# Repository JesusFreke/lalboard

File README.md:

##### lalboard - A 3D-printed keyboard inspired by the DataHand.

## Links
[More Images](https://github.com/JesusFreke/lalboard/wiki/Images)

[120 WPM Typing Demo](https://www.youtube.com/watch?v=oMhOIgrdeE0)

[V2 Project Logs (hackaday.io)](http://lalboard.com)

Online viewer for cluster assemblies:
- [finger](https://a360.co/3vxlLLL)
- [left thumb](https://a360.co/3c63TzE)
- [right thumb](https://a360.co/3c6tvws)

## Project Details
I am a long-time user of a DataHand keyboard. With the scarcity and rising cost of second hand
DataHands these days, I wanted to ensure that I always had access to a DataHand-like keyboard. And
so this project was born.

The overall functionality of the lalboard is obviously heavily based on the DataHand, but I designed
all of the specific key mechanisms, etc. from scratch, to be printable on a normal hobby-level
FDM printer.

With my DataHand, I never felt like I could get the keys positioned *quite right* for my hand. So
one of my primary focuses with the lalboard was adjustability. Each key cluster can be independently
adjusted in all 6 degrees of freedom to some extent.

Most parts need to be printed in a very opaque PLA, but there are a few parts that don't work well
in PLA which should be printed in polycarbonate or similar material, for its strength and heat
resistance.

##### Key Mechanisms

All keys use a pair of magnets to provide the clickiness and key return force, and an IR LED and
phototransistor for detecting a keypress. They are all held in place only with magnets, so they
are easily removable for cleaning, etc.

The feel/clickiness of the keys was another focus area. I tried to get them to feel as similar to
those on a DataHand as possible. They require roughly the same amount of force, and have that same
unique clicky feel due to the magnetic holding force.

##### Adjustability

The key clusters have a trio of standoffs that are designed to be mounted onto a steel sheet with
magnets. Each standoff has an adjustable height, and is mounted to the key cluster via a
ball socket. This provides a limited 6 degrees of freedom in adjusting the angle and position of
each key cluster, in order to get it perfectly positioned for your hands.

##### Electronics

This design uses copper traces that are cut from adhesive-backed copper tape using a vinyl cutter,
and applied to the bottom of 3D-printed "pcbs" printed with polycarbonate for its excellent heat
resistance during soldering. There are currently no designs for actual pcbs, but I don't think it
should be difficult to do. If someone wants to tackle that, I'm happy to give pointers or otherwise
help in any way I can :)

Each side of the keyboard uses an independent teensy 2.0 board, and are connected with 4 wires
between them to enable communication via i2c. Only one side of the keyboard actually needs to be
plugged into USB. The teensy's run a modified version of the
[teensyhand](https://github.com/JesusFreke/teensyhand) firmware.

##### Handrest

The handrest was first molded for my wrist in plasticine clay, and then scanned in using the
[meshroom](https://github.com/alicevision/meshroom) photogrammetry software. Since they were molded
for my wrists specifically, I'm not sure how "one-size-fits-all" they are, or how comfortable they
would be for someone else to use.

##### [BOM](https://github.com/JesusFreke/lalboard/wiki/BOM)

##### [Printing tips & instructions](https://github.com/JesusFreke/lalboard/wiki/Printing-tips-&-instructions)

##### [Preparing the Vinyl-cut PCBs](https://github.com/JesusFreke/lalboard/wiki/Vinyl-Cut-PCBs)

--------

Note: This is not an officially supported Google product.

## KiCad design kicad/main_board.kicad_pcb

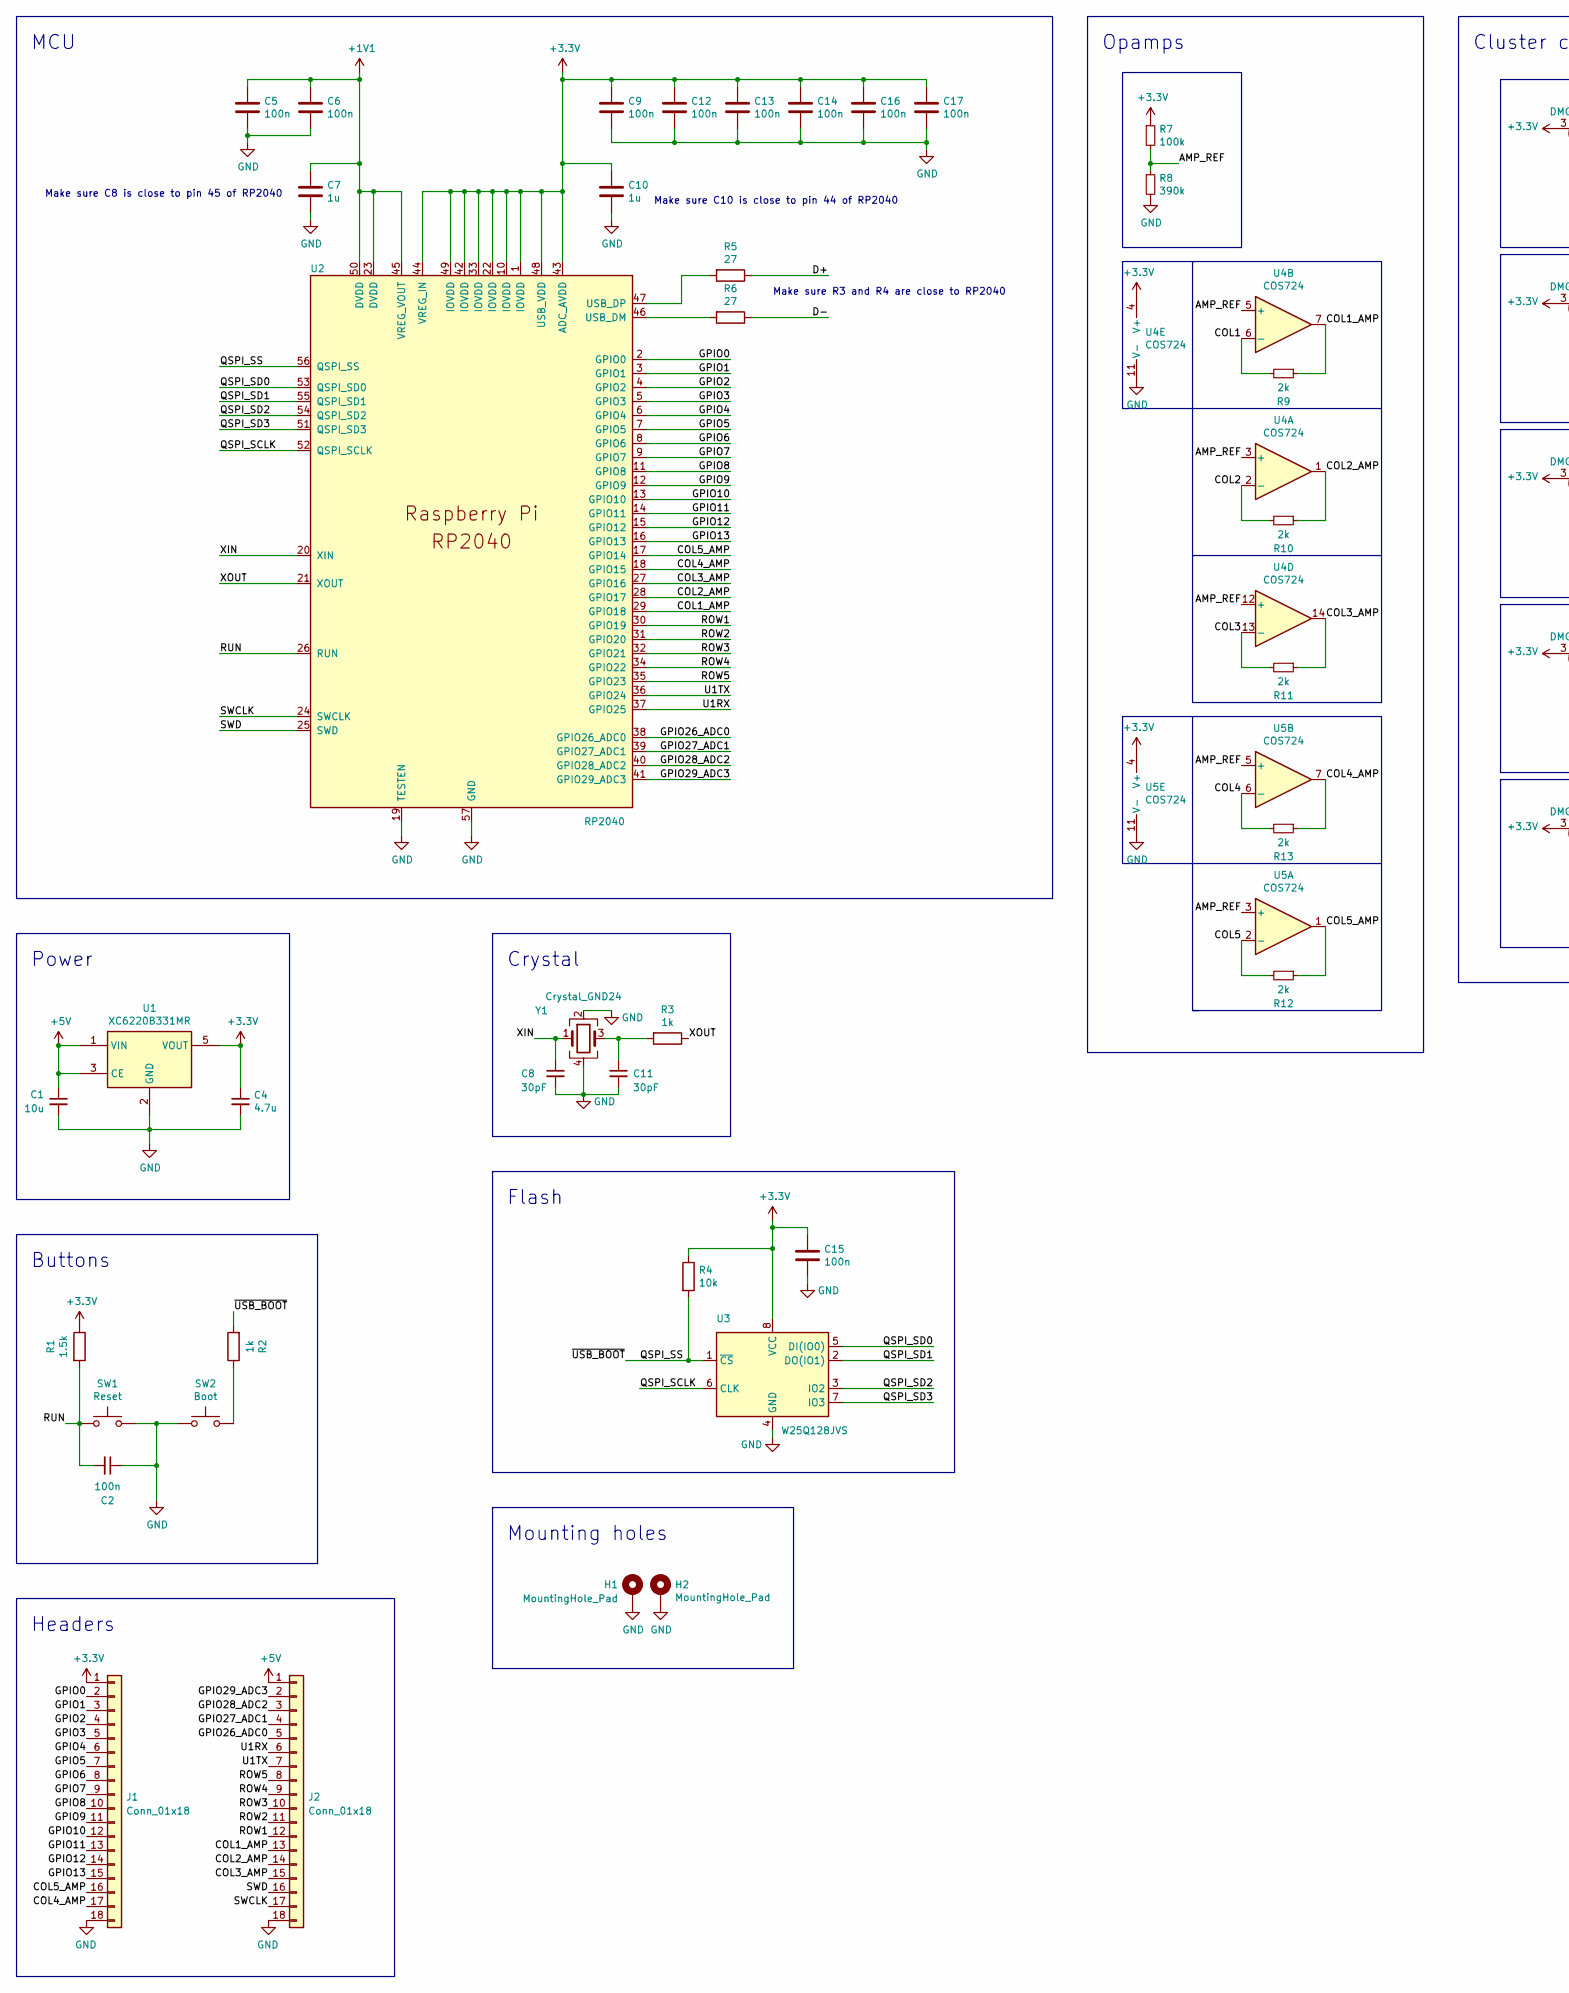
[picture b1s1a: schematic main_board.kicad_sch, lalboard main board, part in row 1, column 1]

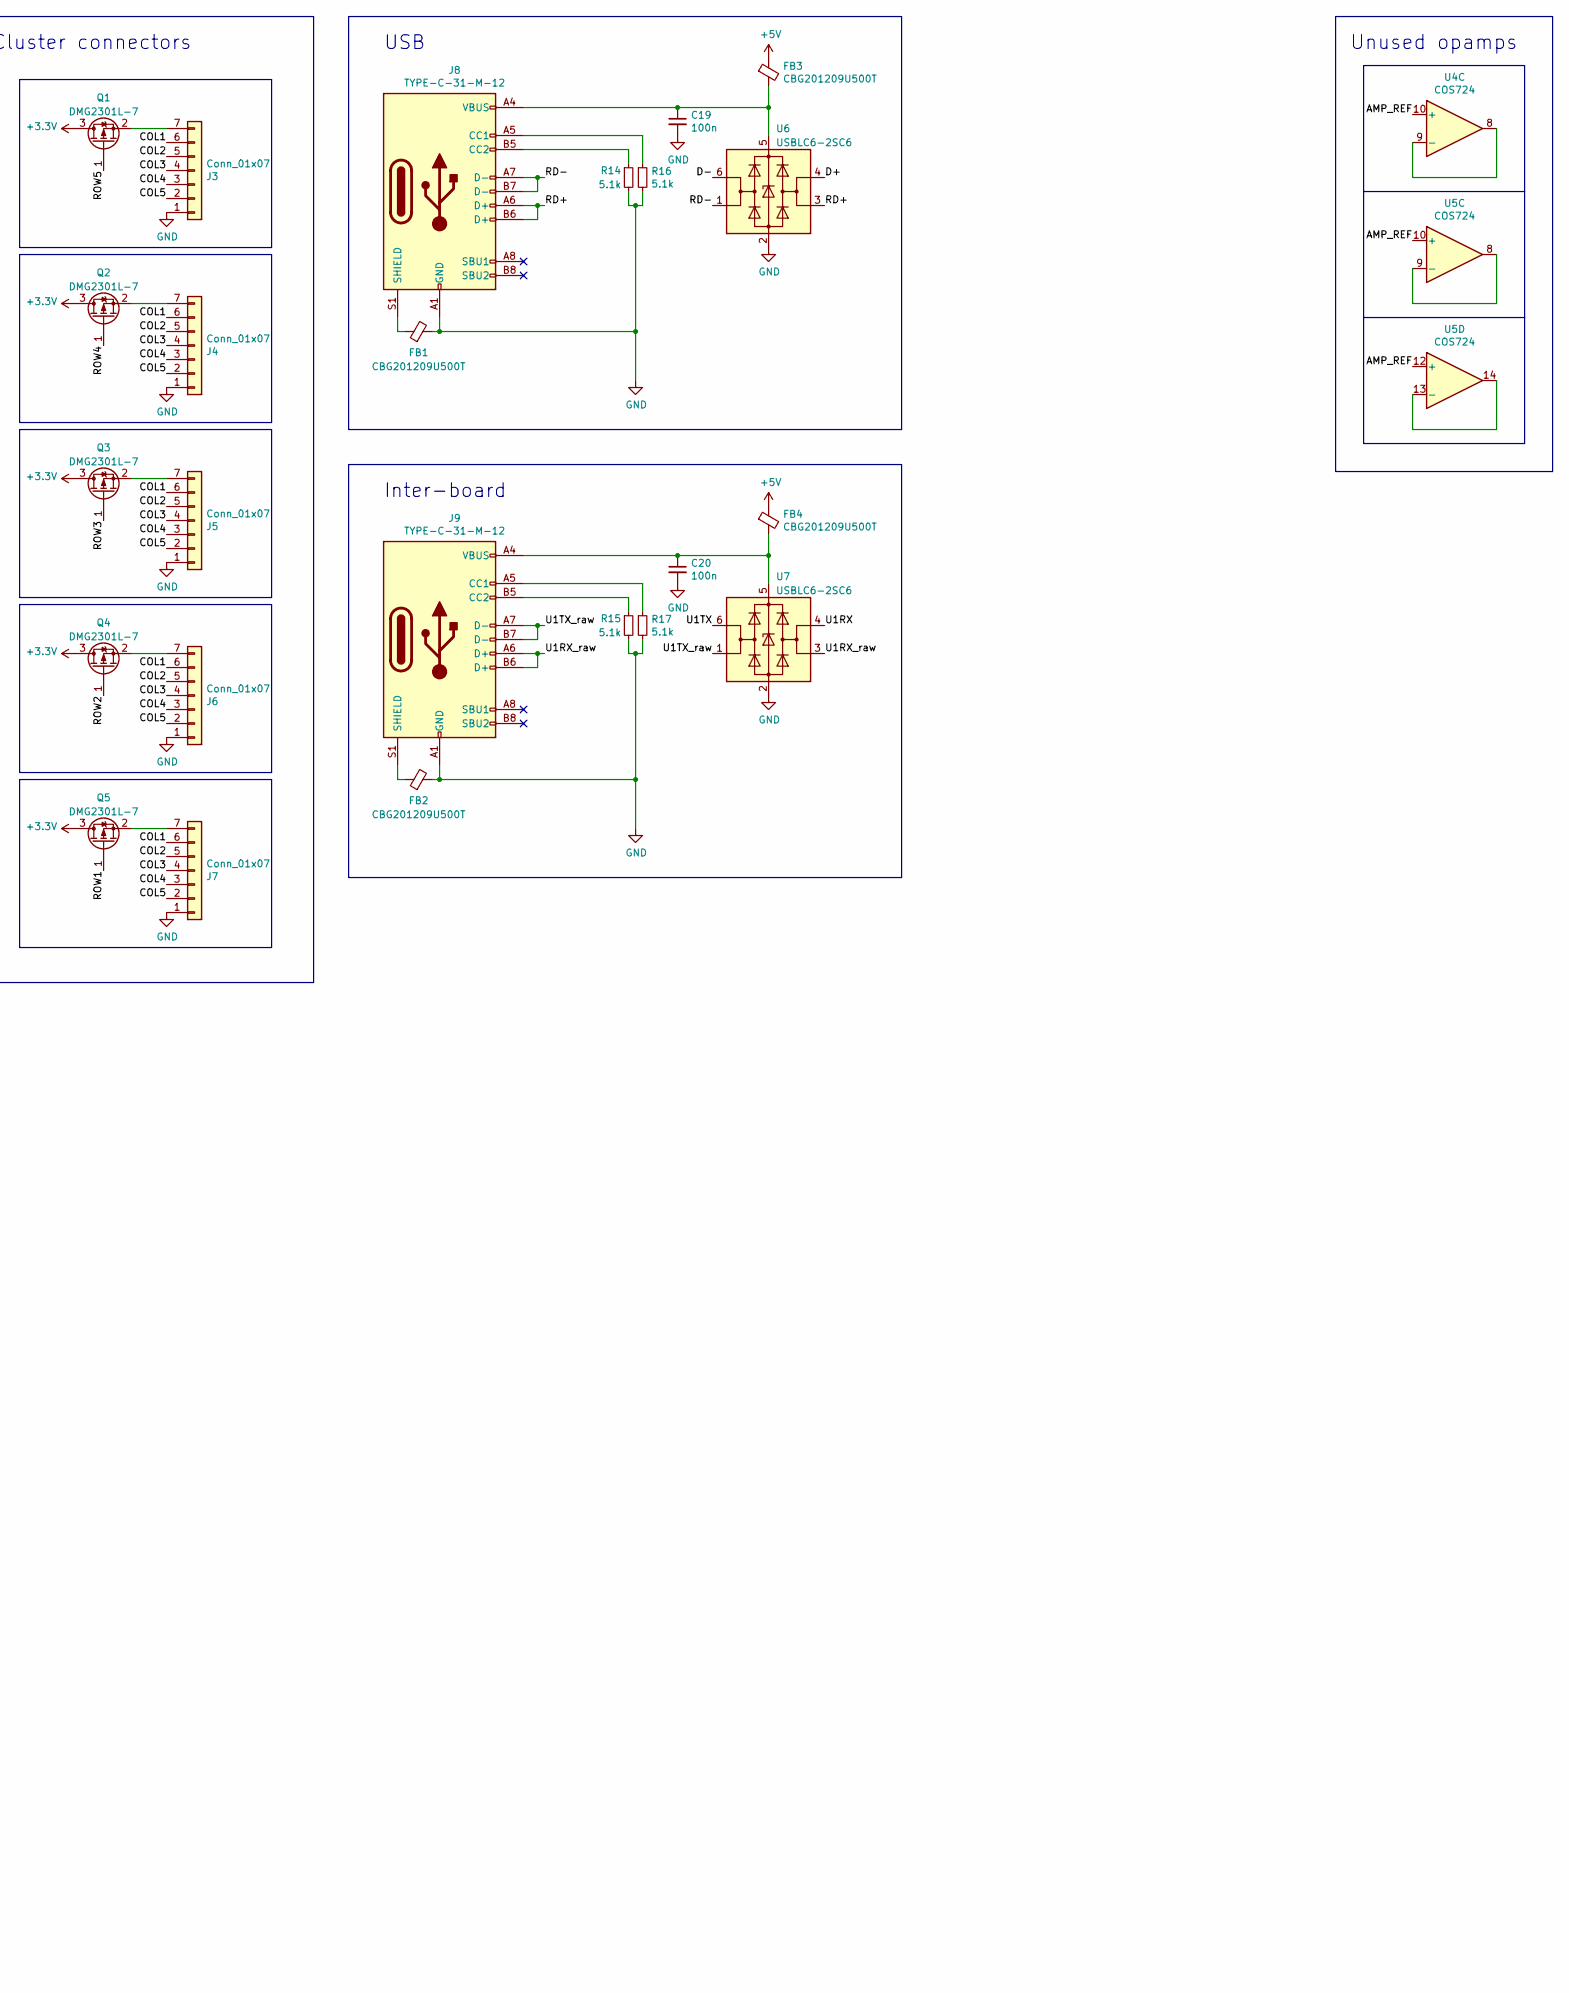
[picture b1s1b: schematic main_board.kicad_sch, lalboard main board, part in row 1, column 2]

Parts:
C1: 10u; C_0402_1005Metric; JLCPCB P/N C15525
C2, C5, C6, C9, C12, C13, C14, C15, C16, C17, C19, C20: 100n; C_0402_1005Metric; JLCPCB P/N C307331
C4: 4.7u; C_0402_1005Metric; JLCPCB P/N C23733
C7, C10: 1u; C_0402_1005Metric; JLCPCB P/N C307454
C8, C11: 30pF; C_0402_1005Metric; JLCPCB P/N C1570
FB1, FB2, FB3, FB4: CBG201209U500T; L_0805_2012Metric; JLCPCB P/N C668236
H1, H2: MountingHole_Pad; MountingHole_3.2mm_M3_DIN965_Pad
J1, J2: Conn_01x18; PinHeader_1x18_P2.54mm_Vertical
J3, J4, J5, J6, J7: Conn_01x07; JST_ZH_B7B-ZR_1x07_P1.50mm_Vertical
J8, J9: TYPE-C-31-M-12; USB_C_Receptacle_HRO_TYPE-C-31-M-12; JLCPCB P/N C165948
Q1, Q2, Q3, Q4, Q5: DMG2301L-7; SOT-23; JLCPCB P/N C102619
R1: 1.5k; R_0402_1005Metric; JLCPCB P/N C25867
R2, R3: 1k; C_0402_1005Metric; JLCPCB P/N C11702
R4: 10k; R_0402_1005Metric; JLCPCB P/N C25744
R5, R6: 27; C_0402_1005Metric; JLCPCB P/N C25771
R7: 100k; R_0402_1005Metric; JLCPCB P/N C25741
R8: 390k; R_0402_1005Metric; JLCPCB P/N C25782
R9, R10, R11, R12, R13: 2k; R_0402_1005Metric_Pad0.72x0.64mm_HandSolder; JLCPCB P/N C4109
R14, R16, R17: 5.1k; R_0402_1005Metric; JLCPCB P/N C25905
R15: 5.1k; R_0402_1005Metric; JLCPCB C25905
SW1: Reset; SW_TS-1187A-B-A-B; JLCPCB P/N C318884
SW2: Boot; SW_TS-1187A-B-A-B; JLCPCB P/N C318884
U1: XC6220B331MR; SOT-23-5; JLCPCB P/N C3040644
U2: RP2040; RP2040-QFN-56; JLCPCB P/N C2040
U3: W25Q128JVS; SOIC-8_5.23x5.23mm_P1.27mm; JLCPCB P/N C97521
U4, U5: COS724; TSSOP-14_4.4x5mm_P0.65mm; JLCPCB P/N C2685541
U6, U7: USBLC6-2SC6; SOT-23-6; JLCPCB P/N C7519
Y1: Crystal_GND24; OSC_X322516MLB4SI; JLCPCB P/N C9002

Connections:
+1V1: C5.1, C6.1, C7.1, U2.23 (DVDD), U2.45 (VREG_VOUT), U2.50 (DVDD)
+3.3V: C4.1, C9.1, C10.1, C12.1, C13.1, C14.1, C15.1, C16.1, C17.1, J1.1, Q1.3 (D), Q2.3 (D), Q3.3 (D), Q4.3 (D), Q5.3 (D), R1.1, R4.1, R7.1, U1.5 (VOUT), U2.1 (IOVDD), U2.10 (IOVDD), U2.22 (IOVDD), U2.33 (IOVDD), U2.42 (IOVDD), U2.43 (ADC_AVDD), U2.44 (VREG_IN), U2.48 (USB_VDD), U2.49 (IOVDD), U3.8 (VCC), U4.4 (V+), U5.4 (V+)
+5V: C1.1, FB3.1, FB4.1, J2.1, U1.1 (VIN), U1.3 (CE)
/AMP_REF: R7.2, R8.1, U4.3 (+), U4.5 (+), U4.10 (+), U4.12 (+), U5.3 (+), U5.5 (+), U5.10 (+), U5.12 (+)
/COL1: J3.6, J4.6, J5.6, J6.6, J7.6, R9.2, U4.6 (-)
/COL1_AMP: J2.13, R9.1, U2.29 (GPIO18), U4.7
/COL2: J3.5, J4.5, J5.5, J6.5, J7.5, R10.2, U4.2 (-)
/COL2_AMP: J2.14, R10.1, U2.28 (GPIO17), U4.1
/COL3: J3.4, J4.4, J5.4, J6.4, J7.4, R11.2, U4.13 (-)
/COL3_AMP: J2.15, R11.1, U2.27 (GPIO16), U4.14
/COL4: J3.3, J4.3, J5.3, J6.3, J7.3, R13.2, U5.6 (-)
/COL4_AMP: J1.17, R13.1, U2.18 (GPIO15), U5.7
/COL5: J3.2, J4.2, J5.2, J6.2, J7.2, R12.2, U5.2 (-)
/COL5_AMP: J1.16, R12.1, U2.17 (GPIO14), U5.1
/D+: R5.1, U6.4 (I/O2)
/D-: R6.1, U6.6 (I/O1)
/GPIO0: J1.2, U2.2 (GPIO0)
/GPIO1: J1.3, U2.3 (GPIO1)
/GPIO2: J1.4, U2.4 (GPIO2)
/GPIO3: J1.5, U2.5 (GPIO3)
/GPIO4: J1.6, U2.6 (GPIO4)
/GPIO5: J1.7, U2.7 (GPIO5)
/GPIO6: J1.8, U2.8 (GPIO6)
/GPIO7: J1.9, U2.9 (GPIO7)
/GPIO8: J1.10, U2.11 (GPIO8)
/GPIO9: J1.11, U2.12 (GPIO9)
/GPIO10: J1.12, U2.13 (GPIO10)
/GPIO11: J1.13, U2.14 (GPIO11)
/GPIO12: J1.14, U2.15 (GPIO12)
/GPIO13: J1.15, U2.16 (GPIO13)
/GPIO26_ADC0: J2.5, U2.38 (GPIO26_ADC0)
/GPIO27_ADC1: J2.4, U2.39 (GPIO27_ADC1)
/GPIO28_ADC2: J2.3, U2.40 (GPIO28_ADC2)
/GPIO29_ADC3: J2.2, U2.41 (GPIO29_ADC3)
/QSPI_SCLK: U2.52 (QSPI_SCLK), U3.6 (CLK)
/QSPI_SD0: U2.53 (QSPI_SD0), U3.5 (DI(IO0))
/QSPI_SD1: U2.55 (QSPI_SD1), U3.2 (DO(IO1))
/QSPI_SD2: U2.54 (QSPI_SD2), U3.3 (IO2)
/QSPI_SD3: U2.51 (QSPI_SD3), U3.7 (IO3)
/QSPI_SS: R2.2, R4.2, U2.56 (QSPI_SS), U3.1 (~CS)
/RD+: J8.A6 (D+), J8.B6 (D+), U6.3 (I/O2)
/RD-: J8.A7 (D-), J8.B7 (D-), U6.1 (I/O1)
/ROW1: J2.12, Q5.1 (G), U2.30 (GPIO19)
/ROW2: J2.11, Q4.1 (G), U2.31 (GPIO20)
/ROW3: J2.10, Q3.1 (G), U2.32 (GPIO21)
/ROW4: J2.9, Q2.1 (G), U2.34 (GPIO22)
/ROW5: J2.8, Q1.1 (G), U2.35 (GPIO23)
/RUN: C2.2, R1.2, SW1.1, U2.26 (RUN)
/SWCLK: J2.17, U2.24 (SWCLK)
/SWD: J2.16, U2.25 (SWD)
/U1RX: J2.6, U2.37 (GPIO25), U7.4 (I/O2)
/U1RX_raw: J9.A6 (D+), J9.B6 (D+), U7.3 (I/O2)
/U1TX: J2.7, U2.36 (GPIO24), U7.6 (I/O1)
/U1TX_raw: J9.A7 (D-), J9.B7 (D-), U7.1 (I/O1)
/XIN: C8.1, U2.20 (XIN), Y1.1
/XOUT: R3.1, U2.21 (XOUT)
GND: C1.2, C2.1, C4.2, C5.2, C6.2, C7.2, C8.2, C9.2, C10.2, C11.2, C12.2, C13.2, C14.2, C15.2, C16.2, C17.2, C19.2, C20.2, FB1.2, FB2.2, H1.1, H2.1, J1.18, J2.18, J3.1, J4.1, J5.1, J6.1, J7.1, J8.A1 (GND), J8.A12 (GND), J8.B1 (GND), J8.B12 (GND), J9.A1 (GND), J9.A12 (GND), J9.B1 (GND), J9.B12 (GND), R8.2, R14.2, R15.2, R16.2, R17.2, SW1.2, SW2.2, U1.2 (GND), U2.19 (TESTEN), U2.57 (GND), U3.4 (GND), U4.11 (V-), U5.11 (V-), U6.2 (GND), U7.2 (GND), Y1.2, Y1.4
unnamed: C11.1, R3.2, Y1.3
unnamed: J3.7, Q1.2 (S)
unnamed: J4.7, Q2.2 (S)
unnamed: J5.7, Q3.2 (S)
unnamed: J6.7, Q4.2 (S)
unnamed: J7.7, Q5.2 (S)
unnamed: J8.A5 (CC1), R16.1
unnamed: J8.B5 (CC2), R14.1
unnamed: FB1.1, J8.S1 (SHIELD)
unnamed: J9.A5 (CC1), R17.1
unnamed: J9.B5 (CC2), R15.1
unnamed: FB2.1, J9.S1 (SHIELD)
unnamed: R2.1, SW2.1
unnamed: R6.2, U2.46 (USB_DM)
unnamed: R5.2, U2.47 (USB_DP)
unnamed: U4.8, U4.9 (-)
unnamed: U5.8, U5.9 (-)
unnamed: U5.13 (-), U5.14
unnamed: C19.1, FB3.2, J8.A4 (VBUS), J8.A9 (VBUS), J8.B4 (VBUS), J8.B9 (VBUS), U6.5 (VBUS)
unnamed: C20.1, FB4.2, J9.A4 (VBUS), J9.A9 (VBUS), J9.B4 (VBUS), J9.B9 (VBUS), U7.5 (VBUS)

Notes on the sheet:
Cluster connectors
Make sure R3 and R4 are close to RP2040
USB
Power
Headers
Buttons
Make sure C8 is close to pin 45 of RP2040
Opamps
Unused opamps
MCU
Inter-board
Crystal
Mounting holes
Make sure C10 is close to pin 44 of RP2040
Flash

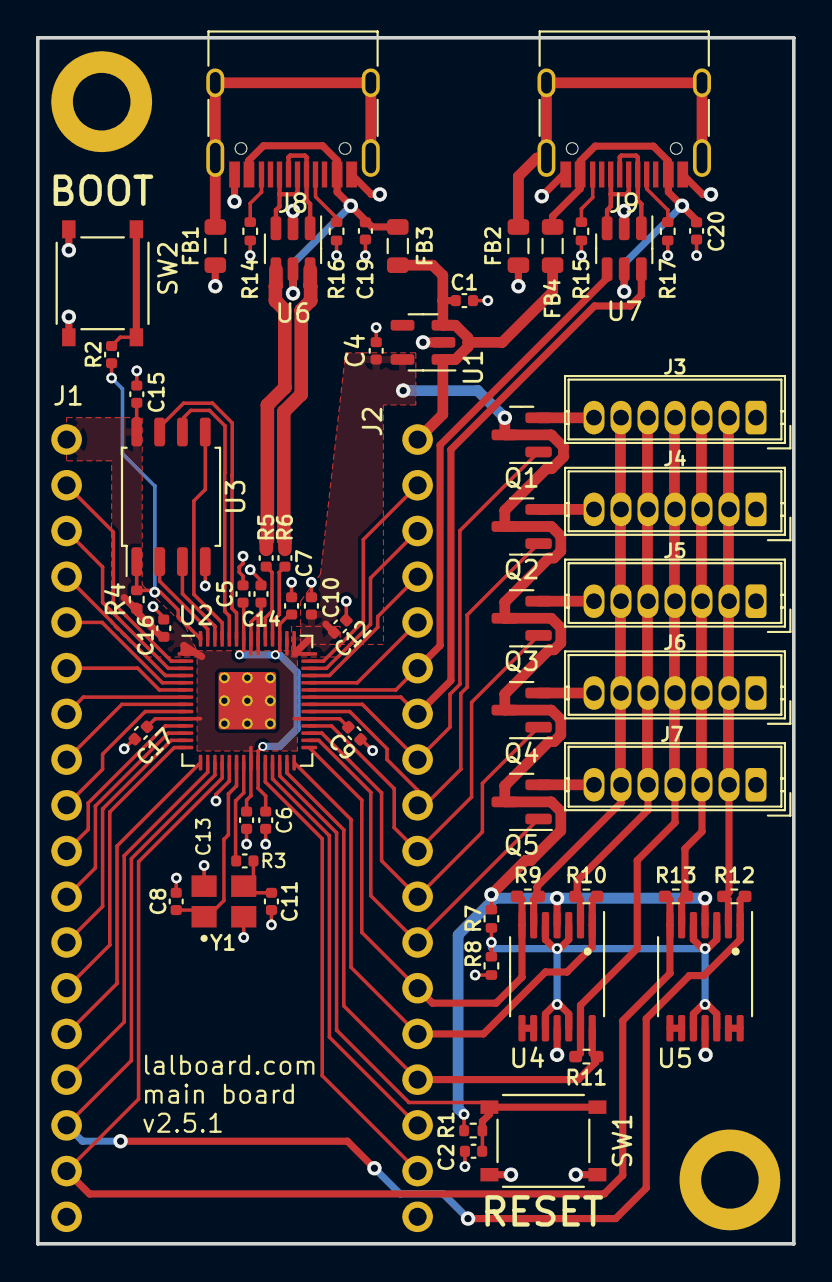
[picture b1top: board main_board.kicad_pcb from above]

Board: 2 copper layers, 42.0 x 67.0 mm, 65 parts (0 on the bottom side), 77 nets.

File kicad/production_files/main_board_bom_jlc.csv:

"Comment","Designator","Footprint","LCSC Part Number"
"10u","C1","C_0402_1005Metric","C15525"
"100n","C2,C5,C6,C9,C12,C13,C14,C15,C16,C17,C19,C20","C_0402_1005Metric","C307331"
"4.7u","C4","C_0402_1005Metric","C23733"
"1u","C7,C10","C_0402_1005Metric","C307454"
"30pF","C8,C11","C_0402_1005Metric","C1570"
"CBG201209U500T","FB1,FB2,FB3,FB4","L_0805_2012Metric","C668236"
"TYPE-C-31-M-12","J8,J9","USB_C_Receptacle_HRO_TYPE-C-31-M-12","C165948"
"DMG2301L-7","Q1,Q2,Q3,Q4,Q5","SOT-23","C102619"
"1.5k","R1","R_0402_1005Metric","C25867"
"1k","R2,R3","C_0402_1005Metric","C11702"
"10k","R4","R_0402_1005Metric","C25744"
"27","R5,R6","C_0402_1005Metric","C25100"
"100k","R7","R_0402_1005Metric","C25741"
"390k","R8","R_0402_1005Metric","C25782"
"2k","R9,R10,R11,R12,R13","R_0402_1005Metric_Pad0.72x0.64mm_HandSolder","C4109"
"5.1k","R14,R15,R16,R17","R_0402_1005Metric","C25905"
"Reset","SW1","SW_TS-1187A-B-A-B","C318884"
"Boot","SW2","SW_TS-1187A-B-A-B","C318884"
"XC6220B331MR","U1","SOT-23-5","C3040644"
"RP2040","U2","RP2040-QFN-56","C2040"
"W25Q128JVS","U3","SOIC-8_5.23x5.23mm_P1.27mm","C97521"
"COS724","U4,U5","TSSOP-14_4.4x5mm_P0.65mm","C2685541"
"USBLC6-2SC6","U6,U7","SOT-23-6","C7519"
"Crystal_GND24","Y1","OSC_X322516MLB4SI","C9002"

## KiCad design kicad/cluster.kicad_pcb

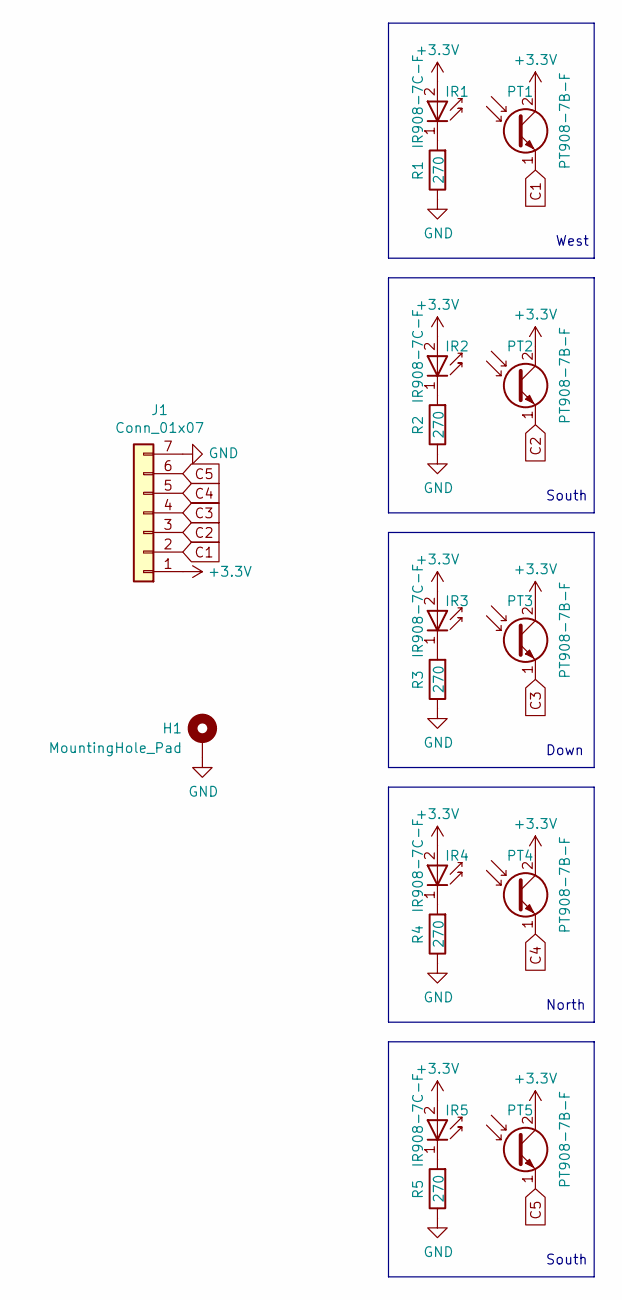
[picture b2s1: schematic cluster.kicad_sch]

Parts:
H1: MountingHole_Pad; MountingHole_3.2mm_M3_DIN965_Pad
IR1, IR2, IR3, IR4, IR5: IR908-7C-F
J1: Conn_01x07; JST_ZH_S7B-ZR_1x07_P1.50mm_Horizontal
PT1, PT2, PT3, PT4, PT5: PT908-7B-F; PT908-7C-F
R1, R2, R3, R4, R5: 270; R_0805_2012Metric_Pad1.20x1.40mm_HandSolder

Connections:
+3.3V: IR1.2 (A), IR2.2 (A), IR3.2 (A), IR4.2 (A), IR5.2 (A), J1.1, PT1.2 (C), PT2.2 (C), PT3.2 (C), PT4.2 (C), PT5.2 (C)
C1: J1.2, PT1.1 (E)
C2: J1.3, PT2.1 (E)
C3: J1.4, PT3.1 (E)
C4: J1.5, PT4.1 (E)
C5: J1.6, PT5.1 (E)
GND: H1.1, J1.7, R1.1, R2.1, R3.1, R4.1, R5.1
unnamed: IR1.1 (K), R1.2
unnamed: IR2.1 (K), R2.2
unnamed: IR3.1 (K), R3.2
unnamed: IR4.1 (K), R4.2
unnamed: IR5.1 (K), R5.2

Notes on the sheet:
Down
North
West
South

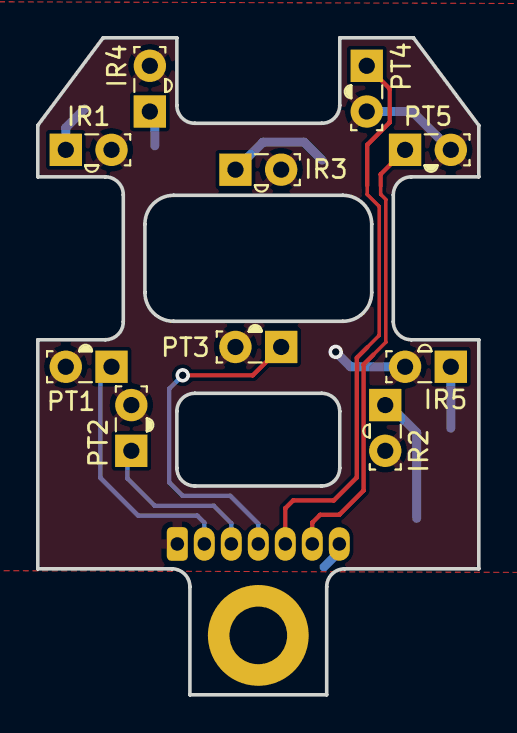
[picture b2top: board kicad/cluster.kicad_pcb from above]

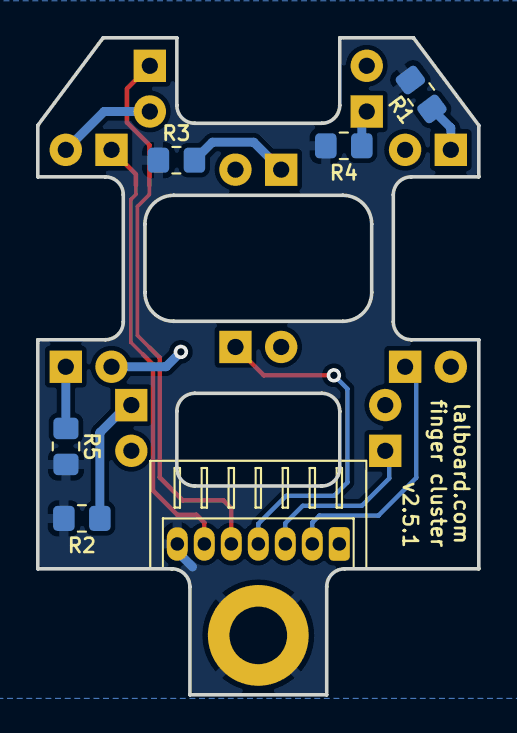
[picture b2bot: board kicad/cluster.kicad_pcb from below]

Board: 2 copper layers, 24.5 x 36.5 mm, 17 parts (6 on the bottom side), 12 nets.

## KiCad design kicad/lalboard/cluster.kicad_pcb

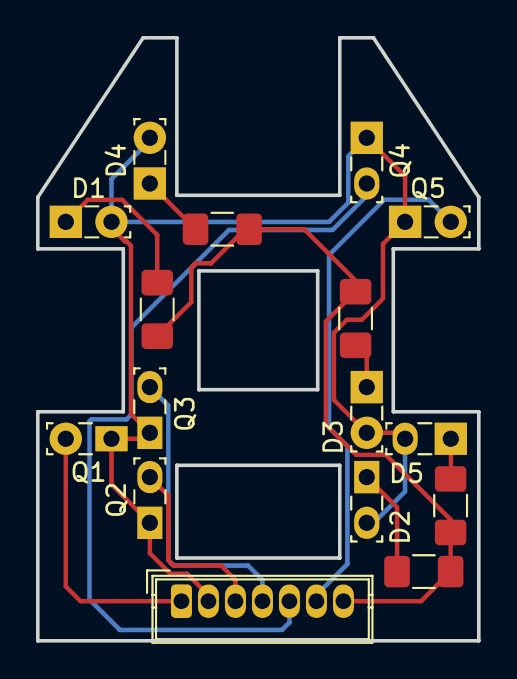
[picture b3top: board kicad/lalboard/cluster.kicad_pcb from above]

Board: 2 copper layers, 24.5 x 33.5 mm, 16 parts (0 on the bottom side), 12 nets.

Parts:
D1, D2, D3, D4, D5: IR908-7C-F; LED_SideEmitter_Rectangular_W4.5mm_H1.6mm
J1: Conn_01x07; JST_ZH_B7B-ZR_1x07_P1.50mm_Vertical
Q1, Q2, Q3, Q4, Q5: PT908-7B-F; LED_SideEmitter_Rectangular_W4.5mm_H1.6mm
R1, R2, R3, R4, R5: 150; R_1206_3216Metric_Pad1.42x1.75mm_HandSolder

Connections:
+5V: D1.2, D2.2, D3.2, D4.2, D5.2, J1.2, Q1.1, Q2.1, Q3.1, Q4.1, Q5.1
C1: J1.1, Q1.2
C3: J1.3, Q2.2
C4: J1.4, Q3.2
C5: J1.5, Q4.2
C6: J1.6, Q5.2
GND: J1.7, R1.1, R2.1, R3.1, R4.1, R5.1
unnamed: D1.1, R1.2
unnamed: D2.1, R2.2
unnamed: D3.1, R3.2
unnamed: D4.1, R4.2
unnamed: D5.1, R5.2

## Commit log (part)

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2019-02-11 Initial side_key implementation
2019-02-11 Implement the center key
2019-02-11 Add initial key cluster, with 4 key bases
2019-02-11 Add the thumb pcb and the central pcb
2019-02-11 Tweak the retaining ridge geometry
2019-02-11 Tweak the thread size of the screwballs
2019-02-11 Tweak the hole size for the jst connector
2019-02-11 Tweak the retaining groove size and depth for the side keys
    This makes it a bit deeper, so the drooping overhangs don't fall all the
    way to the bed and prevent the groove from gripping.
    This also shrinks the width of the groove a bit, to give a bit more space
    between it and the magnet hole, for better printability
2019-02-11 Start implementing cluster with the initial 4 vertical key bases
2019-02-11 Fillet for the edges on the central magnet riser
    This should help reduce binding when pressing on the edge of the center
    key
2019-02-11 Redesign the thumb mode key
    This new design prevents the upward force by the thumb that was causing
    the previous design to slip out of the base.
2019-02-11 Reduce the key angle of the inner thumb key to 7
    I thought the previous angle of 10 felt good, but it turned out the key
    was stopping early, because it was hitting the key base of the mode key,
    so it wasn't actually moving the full 10 degrees.
2019-02-11 Add a key breakout board
    This has 2 JST connectors and a normal male header, which can be inserted
    between a key module and the central pcb, or between the two sides, to
    allow access to the signals for debugging purposes.
2019-02-11 Add the main thumb side keys
2019-02-11 Refactor how the led/phototransistor cavities are handled
    It now uses split faces that must be extended by the caller
2019-02-11 Add a thin base for the proximal ballsocket on the thumb module
2019-02-11 Tweak the design of the center key
    There's now a single post in the middle of the key, along with a protrusion
    to block the light when pressed. In the cluster, there's a central hole
    that the post is inserted in to.
    The post is also lengthened, so it extends to the bottom of the cluster in
    the neutral position, which requires a corresponding hole in the PCB now
    too.
2019-02-11 Don't return a separate negatives component from ball_socket_base
2019-02-11 Tweak the thin magnet cutout size, and use it for all screwball bases
2019-02-11 Add a longer ballscrew definition, for the back of the key modules
2019-02-12 Add exported stls for all of the models
2019-02-17 Create a docs folder and add some images
2019-02-23 Make the center down key post a square
    The previous circular post with a flat face had a tendency to get wedged
    into the hole if the key was rotated while pressing it
2019-02-25 Increase the height of the light interruptor on the center down key
    It wasn't blocking enough light to trigger the key
2019-02-28 Change the rotation of the magnet pair for the central down key back to horizontal
    The rotated magnet doesn't feel quite as clicky
2019-03-01 Get rid of the peaked magnet hole, and move the center magnets down a bit more
    The peaked magnet hole worked, but I didn't particularly like how it looked.
    This changes it back to the older squarish magnet hole.
    The nubbin on the center key was still interfering with the pliers a bit
    when inserting the magnet, so this also moves the magnets down a bit
    further.
2019-03-14 Increase the width of the groove on the back of the thumb mode key
    Due to the way the mode key in particular tends to get torqued, there would
    be an annoying click as the groove just catches on the corresponding ridge,
    and then slips past it.
2019-07-31 Add hand rest components
2019-08-01 Increase vertical space below board frame to account for longer Teensy pins
2019-08-08 Add board textures for rendering
2019-08-23 Reduce drill size of resistor holes. Fix right thumb cluster
2019-12-13 Add connection topic
    Also decrease image size
2019-12-15 Improve documentation
2020-06-29 Add a small cutout to help with inserting the "lower outer" magnet on the thumb
2020-06-29 Fix uses of Union.add
    This method was removed in fscad
2020-08-14 Fix the right handrest
    It was previously the same as the left hand side.
2020-10-10 Switch the clusters to use a new magnetic attachment mechanism
2020-10-18 Name the phototransistor and led cavities
2020-10-20 First part of making a solid top cluster
2020-10-20 Make the bottom of the key well a V instead of circular
    This makes the key well more easily printable upside-down without supports
2020-10-20 Make the light interruptor post on the center key a bit thinner
    The hole was made a bit thinner in the cluster refactor, and this helps
    to keep it from binding on the side
2020-10-26 Add a cutout for the connector legs on the underside of the cluster
2020-10-26 Add a cluster_assembly part script
    This creates the cluster, the pcb and the front and back clips in-situ.
2020-10-29 Starting design of new thumb cluster
2020-10-30 Add the remaining keys to the full thumb assembly
2020-11-01 Widen the slot behind the down key
    This allows easier insertion for the magnet in the lower outer key well.
    This also adds an extension to the back of the down key to cover over the
    extra gap, just so it looks nicer.
2020-11-01 Get rid of the old insertion cutout for the lower outer keywell
    The cutout wasn't present in the new design anyway, and I wasn't have
    any issues inserting the magnets without it.
2020-11-03 Move the kicad files up a directory
2020-11-03 Add kicad pcb design for left thumb
2021-03-09 Simplify the front of the cluster, and add a prototype cluster mount plate
2021-03-11 Restructure how the cluster parts are organized
    - rename the former "cluster_design" to "base_cluster_design"
    - add a new "cluster_design" that is only the base cluster, along with the front and back extensions
    - add the new front clip to cluster_assembly
2021-04-24 Extract stls directory into a submodule
2021-04-24 Extract the screw nut design out to a separate method in lalboard.py
    This allows it to be used in other assemblies without having to specify
    its parameters in multiple places.
2021-04-24 Fillet the center hole in the cluster pcb, and adjust its offset
2021-04-24 Update the exported thumb parts
2021-04-24 Fix the pad sizes on the cluster pcb design
    The custom sizes had apparently gotten lost in the last commit
    for the kicad stuff.
2021-04-24 Update the design of the left thumb cluster pcb
2021-04-24 Add nut recesses in the thumb clusters, for screws to hold down the PCB
2021-04-24 Fix up the cluster and thumb_cluster_left pcbs
    Some of the nets for the pours and screw holes had gotten unassigned
    somehow
2021-04-24 Fix the orientation of the magnet void in the base for the screw supports
    The void was flipped vertically, so that the widening insertion taper was
    at the bottom of the hole. This also embiggens the holes slightly, to make
    sure they're able to slip in.
2021-04-24 Add a bit more space at the lower outer part of the pcb
    This gives more space to get a trace out of that little cramped area
    in the bottom
2021-04-24 Fillet the remaining sharp corners on the thumb cluster
    It seems silly to have 2 sharp corners, with the rest being filleted
2021-04-24 Use cardinal directions as names for the cluster side key bases
    I think this is a bit clearer, and is the nomenclature I usually use when
    referring to a specific key.
2021-04-24 Add support for the filleted key wells to vertical_key_base
    Also refactor base_cluster_design to use this
2021-04-24 Fillet the keywells on the thumb clusters
2021-04-24 Add a fillet to the attachment cutouts on the thumb pcb
2021-04-28 Tweak the nut cutouts
    On the finger cluster, the nut cutout was 2.6mm tall, but it wasn't aligned
    with a .2mm layer line, so it was actually 2.8mm tall once sliced. This
    increases the size to 2.8mm and aligns it to a .2mm layer line.
    For the thumb clusters, the size was 2.6mm tall and it was already aligned,
    but 2.6mm was a bit too short and the nut didn't fit. This increases the
    size to 2.8mm.
2021-05-09 Tweak the thumb mode keys for better printability
    This adds a small "extension" to the beginning of the angled part that
    keeps it attached to the bed. The very first part of the slope up would
    always merge too strongly with the supports, leaving a bit of support
    material on the back.
    This gives a bit more vertical room at the point where the supports start,
    to help alleviate this problem.
2021-05-18 Update the handrest model to a brep based on a t-spline
    This is a t-spline that I modeled and fit to the original handrest mesh.
    The t-spline should be more easily editable if needed.
2021-05-22 Add a "bottom" named face for the central_pcb
    This avoids having to find the bottom face in the part script, and anywhere
    else it might be used.
2021-05-24 Add a full assembly for the left and right sides, using the new steel base
2021-05-29 Disable exporting assemblies to the cloud by default in export_parts
2021-06-01 Fix the thumb pcb for positioned_thumb_assembly for the left hand
2021-06-05 Remove some unused components and other dead code
2021-06-06 Reduce the travel angle of the thumb down key from 9 to 7 degrees
    The key was triggering a bit too early/releasing a bit too late, causing
    the shift key to accidentally be held down for a key after the intended
    key.
    This will cause the key to bottom out sooner, so that there should be less
    delay from starting to release the key to when it actually triggers the
    key up event.
2021-06-09 Reverse the cluster connectors on the main board
    This reverses the connectors, so the orientation is correct for a normally
    wired cable.
2021-06-14 Add a light interruptor on the bottom of the thumb down key
    This adds a small protrusion on the bottom that ensures the light path is
    fully blocked when the key is fully pressed.
2021-06-14 Update the stls for the recent changes to the thumb cluster
2023-10-10 Add a front magnet to the clusters
    Add a magnet, instead of that silly clip thing.
    An extra clip on the front isn't normally needed now, but one can
    be added in cases where the front of the cluster is too low to the
    base plate, to give a bit more room for the support underneath.
    This also tweaks the static supports to have another magnet at the
    front to attach to the cluster, and moves the cord slot a bit, to
2023-10-30 Update the main board for v2.5
    This switches from an ESP32 MCU to an RP2040
2023-11-18 Main board v2.5.1
    - Remove the decoupling capacitor on the boot selection button
    - Fix the part selection in the BOM for the 27 ohm usb series resistors
    (old part was mistakenly a 27kohm resistor)
